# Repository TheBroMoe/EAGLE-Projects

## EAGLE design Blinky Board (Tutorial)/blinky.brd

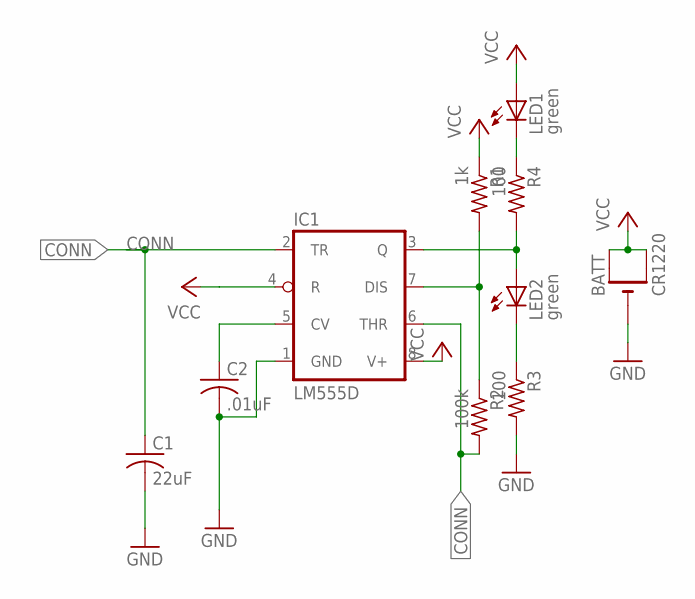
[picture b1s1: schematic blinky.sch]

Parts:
BATT: CR1220; CR1220-SMD
C1: 22uF; C0805; MPN MC0805B224K500A5.08MM
C2: .01uF; C0805; MPN 26884
IC1: LM555D; SO08; MPN TLC555CP
LED1, LED2: green; CHIPLED_0805; MPN MCL-S270GC
R1: 1k; R0805; MPN ERJ-1GNF1001C
R2: 100k; R0805; MPN MCTF0805BTC1003
R3, R4: 100; R0805; MPN CRCW080510R0FKEA

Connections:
CONN: C1.1, IC1.2 (TR), IC1.6 (THR), R2.2
GND: BATT.-, C1.2, C2.2, IC1.1 (GND), R3.2
unnamed: LED1.C, R4.1
unnamed: IC1.3 (Q), LED2.A, R4.2
unnamed: LED2.C, R3.1
unnamed: IC1.7 (DIS), R1.2, R2.1
unnamed: C2.1, IC1.5 (CV)
VCC: BATT.+$1 (+), BATT.+$2 (+1), IC1.4 (R), IC1.8 (V+), LED1.A, R1.1

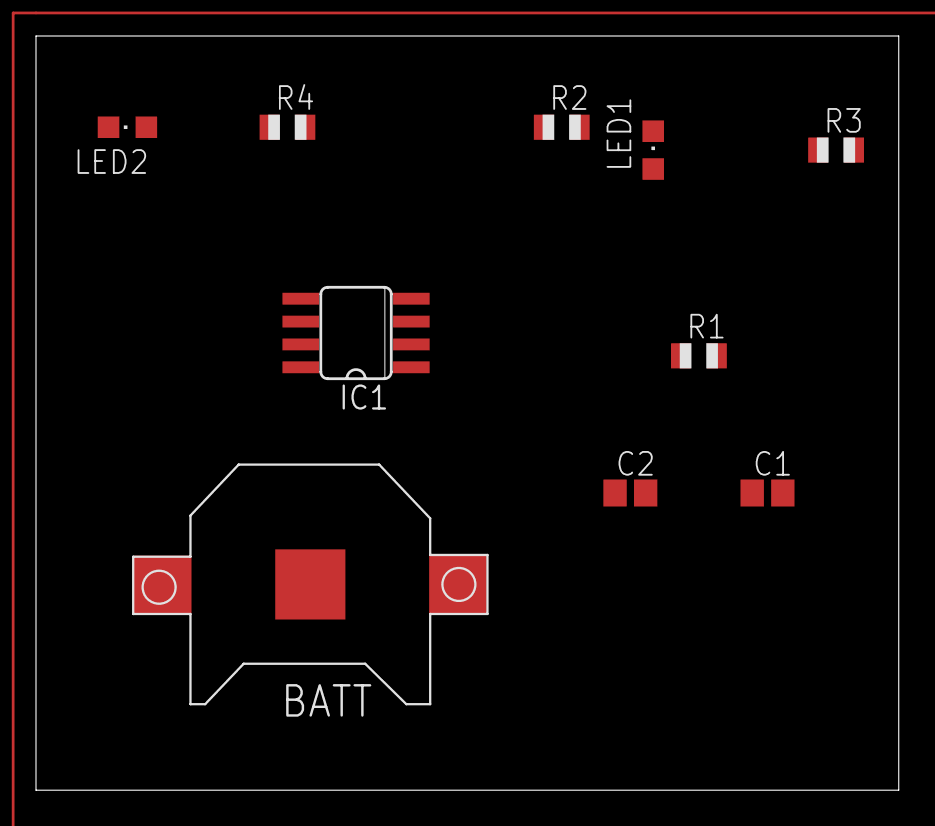
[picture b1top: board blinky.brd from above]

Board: 2 copper layers, 47.9 x 41.9 mm, 10 parts (0 on the bottom side), 8 nets.

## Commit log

2018-09-21 add first project
2018-09-29 add project and adafruit
2018-09-29 add blinky schematic and order
2018-09-29 generate blinky board
2018-09-29 up to date
2018-11-10 add mid level schematic
2018-11-17 add complete protection board
2018-11-17 add schematic photos
2018-11-17 add readme.md for protection element
2018-11-20 remove battery and load from schematic
2018-11-20 add net labels to schematic
2018-11-22 update board
2018-11-22 update zener diode and element order
2018-11-22 update LTspice schematic
2018-11-23 update schematic and board
2018-11-23 add pictures
2018-11-23 add order list
2018-11-23 add datasheets
2018-11-23 update ltspice asc
